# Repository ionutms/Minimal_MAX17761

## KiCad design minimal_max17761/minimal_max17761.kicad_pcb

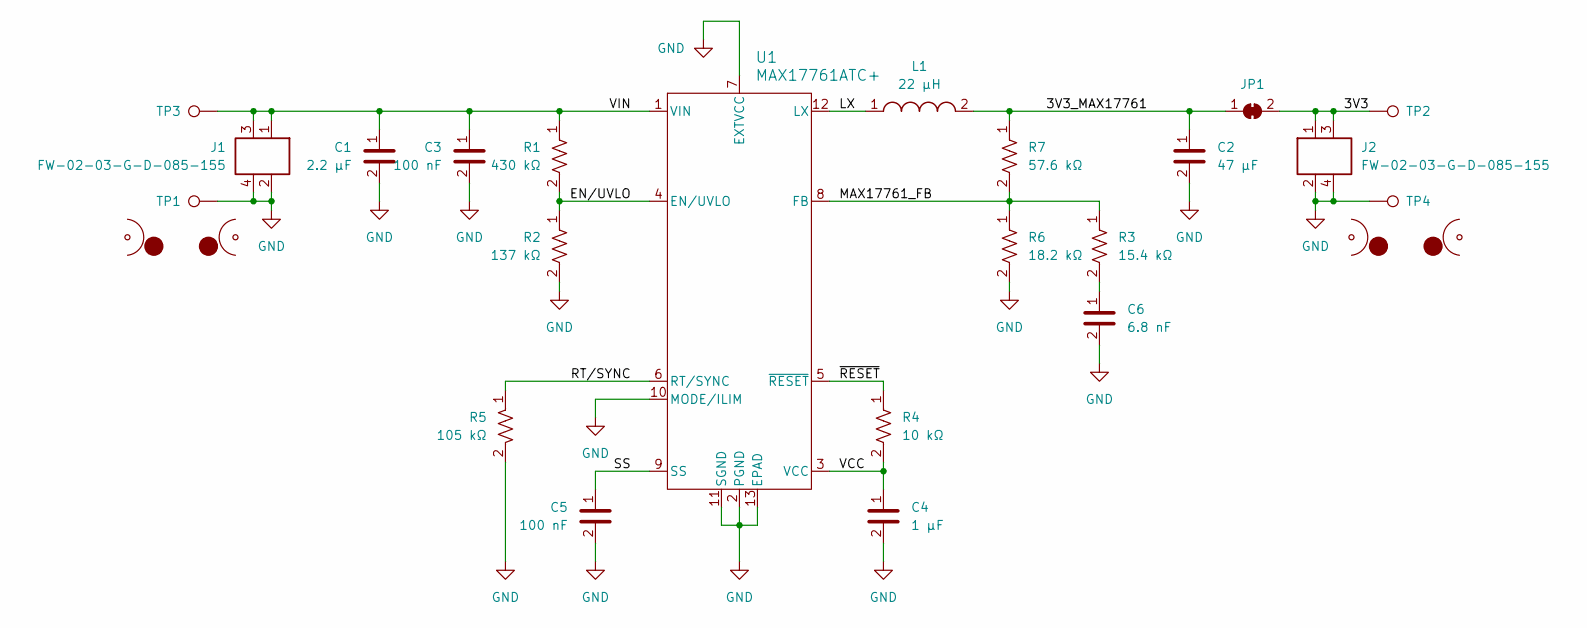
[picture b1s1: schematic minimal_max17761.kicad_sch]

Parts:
C1: 2.2 µF; C_1206_3216Metric; Voltage Rating DC 50 VDC; Tolerance 10%; MPN KGM31HR71H225KU
C2: 47 µF; C_1210_200_3225Metric; Voltage Rating DC 10 VDC; Tolerance 10%; MPN GRM32ER71A476KE15L
C3, C5: 100 nF; C_0402_1005Metric; Voltage Rating DC 50 VDC; Tolerance 10%; MPN GCM155R71H104KE02D
C4: 1 µF; C_0402_1005Metric; Voltage Rating DC 16 VDC; Tolerance 10%; MPN C1005X6S1C105K050BC
C6: 6.8 nF; C_0402_1005Metric; Voltage Rating DC 50 VDC; Tolerance 10%; MPN AC0402KRX7R9BB682
J1, J2: FW-02-03-G-D-085-155; Current Rating (A) 5.2; Voltage Rating (V) 300; MPN FW-02-03-G-D-085-155
JP1: SolderJumper_2_Bridged; SolderJumper-2_P1.3mm_Bridged_RoundedPad1.0x1.5mm
L1: 22 µH; XAL5050; Tolerance ±20%; MPN XAL5050-223ME
MB1, MB2: mouse-bite-midle-50mil-200mil
R1: 430 kΩ; R_0402_1005Metric; Voltage Rating 50V; Tolerance 1%; MPN ERJ-2RKF4303X
R2: 137 kΩ; R_0402_1005Metric; Voltage Rating 50V; Tolerance 1%; MPN ERJ-2RKF1373X
R3: 15.4 kΩ; R_0402_1005Metric; Voltage Rating 50V; Tolerance 1%; MPN ERJ-2RKF1542X
R4: 10 kΩ; R_0402_1005Metric; Voltage Rating 50V; Tolerance 1%; MPN ERJ-2RKF1002X
R5: 105 kΩ; R_0402_1005Metric; Voltage Rating 50V; Tolerance 1%; MPN CRCW0402105KFKED
R6: 18.2 kΩ; R_0402_1005Metric; Voltage Rating 50V; Tolerance 1%; MPN ERJ-2RKF1822X
R7: 57.6 kΩ; R_0402_1005Metric; Voltage Rating 50V; Tolerance 1%; MPN CRCW040257K6FKED
TP1, TP2, TP3, TP4: TestPoint; TestPoint_THTPad_Castelated
U1: MAX17761ATC+; 21-0664_TD1233&plus_1C_MXM; MPN MAX17761ATC+

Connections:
/3V3: J2.1, J2.3, JP1.2, TP2.1
/3V3_MAX17761: C2.1, JP1.1, L1.2, R7.1
/EN/UVLO: R1.2, R2.1, U1.4 (EN/UVLO)
/LX: L1.1, U1.12 (LX)
/MAX17761_FB: R3.1, R6.1, R7.2, U1.8 (FB)
/RT/SYNC: R5.1, U1.6 (RT/SYNC)
/SS: C5.1, U1.9 (SS)
/VCC: C4.1, R4.2, U1.3 (VCC)
/VIN: C1.1, C3.1, J1.1, J1.3, R1.1, TP3.1, U1.1 (VIN)
/~RESET: R4.1, U1.5 (~RESET)
GND: C1.2, C2.2, C3.2, C4.2, C5.2, C6.2, J1.2, J1.4, J2.2, J2.4, R2.2, R5.2, R6.2, TP1.1, TP4.1, U1.2 (PGND), U1.7 (EXTVCC), U1.10 (MODE/ILIM), U1.11 (SGND), U1.13 (EPAD)
unnamed: C6.1, R3.2

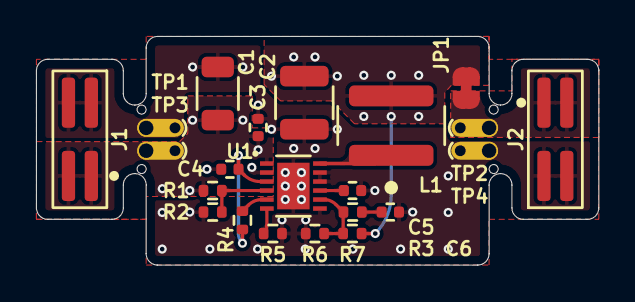
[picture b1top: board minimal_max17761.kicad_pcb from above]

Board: 4 copper layers, 31.2 x 12.7 mm, 24 parts (0 on the bottom side), 12 nets.

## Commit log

2025-03-11 Add initial KiCad project files for minimal_max17761
2025-03-11 Add submodule for KiCAD Symbol Generator
2025-03-11 Add footprint and symbol library tables for KiCad project
2025-03-12 Update KiCAD Symbol Generator submodule and add configuration and PDF files for minimal_max17761 project
2025-03-12 Update minimal_max17761.pdf with formatting adjustments and additional details
2025-03-12 Add minimal_max17761.glb file for project assets
2025-03-16 Remove KiCAD Symbol Generator submodule from project
2025-03-16 Add KiCAD Symbols Generator submodule to the project
2025-03-16 Update footprint library URIs to use KiCAD_Symbols_Generator
2025-03-17 Add log and JSON files to .gitignore
2025-03-17 Switch to KiCad 9
2025-03-17 Add board 3D step model
2025-03-17 Update board 3D step model
2025-03-18 Backup
2025-03-18 Update subproject commit for KiCAD Symbols Generator
2025-03-18 Update component blacklist and UUIDs in PCB configuration
2025-03-19 Add job set configuration for minimal_max17761 PCB export and rendering
2025-03-19 Update PCB layout
2025-03-19 Add minimal_max17761 side image and updated GLB and WRL files
2025-03-19 Update output path in job set configuration to use project variable
2025-03-19 Replace JPG with PNG for minimal_max17761 side image and remove obsolete job set configuration
2025-03-19 Refactor job set configuration for minimal_max17761 to streamline PCB export command and update job type
2025-03-19 Update GLB and PNG files for minimal_max17761
2025-03-20 Add output filename and new render command to job set configuration for minimal_max17761
2025-03-20 Add new assets and update step file reference for minimal_max17761
2025-03-21 Update job set configuration for minimal_max17761 to specify output paths and filenames for GLB and PNG exports
2025-03-21 Remove old images and add new picture assets and 3D model for minimal_max17761
2025-03-21 Update output filenames in job set configuration for minimal_max17761 exports
2025-03-21 Add new GLB 3D model for minimal_max17761
2025-04-18 Update default zoom factor in kicad-config.yml to improve visibility
2025-04-18 Update KiCad documentation (schematics and PCB renders)
2025-04-18 Update default zoom factor in kicad-config.yml to enhance visibility
2025-04-25 Refactor KiCad configuration and update job workflow for improved output handling
2025-04-25 Remove unused schematic and image files for minimal MAX17761 design
2025-04-25 Update KiCad documentation for minimal_max17761 (schematics and PCB renders)
2025-04-25 Update side view zoom factor and pan settings in kicad-config.yml for improved visualization
2025-05-07 Development Backup
2025-05-22 Add GitHub Actions workflow to generate KiCad documentation and 3D models
2025-05-22 Update branch trigger for KiCad documentation generation workflow
2025-05-22 Rename workflow to reflect purpose: Generate KiCad 3D Models
2025-05-22 Rename job to generate KiCad 3D models and streamline file handling in workflow
2025-05-22 Add KiCad 3D models for minimal_max17761
2025-05-22 Refactor workflow to read permissions and remove unnecessary steps for default branch handling
2025-05-23 Enhance workflow by adding cleanup step for old 3D model artifacts and improving permissions
2025-05-25 Update workflow trigger branch to 'doc_workflow' for KiCad 3D models generation
2025-08-18 Update KiCad configuration and workflow files
2025-08-22 Update workflows to trigger 3D model generation
2025-08-29 Update KiCad Docker image version and add Interactive HTML BOM generation
2025-10-05 chore: update workflows from central repository
2025-10-05 chore: update workflows and kicad config from central repository
2025-10-26 Update kicad-config workflow settings
